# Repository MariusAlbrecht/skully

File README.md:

# skully

A split, wireless, ergo keybaord inspired by weteor's [3w6](https://github.com/weteor/3W6) and built with MrZealot's [ergogen](https://github.com/ergogen/ergogen).

The overall shape of one side reminded me of a skull, thus the name and silkscreen

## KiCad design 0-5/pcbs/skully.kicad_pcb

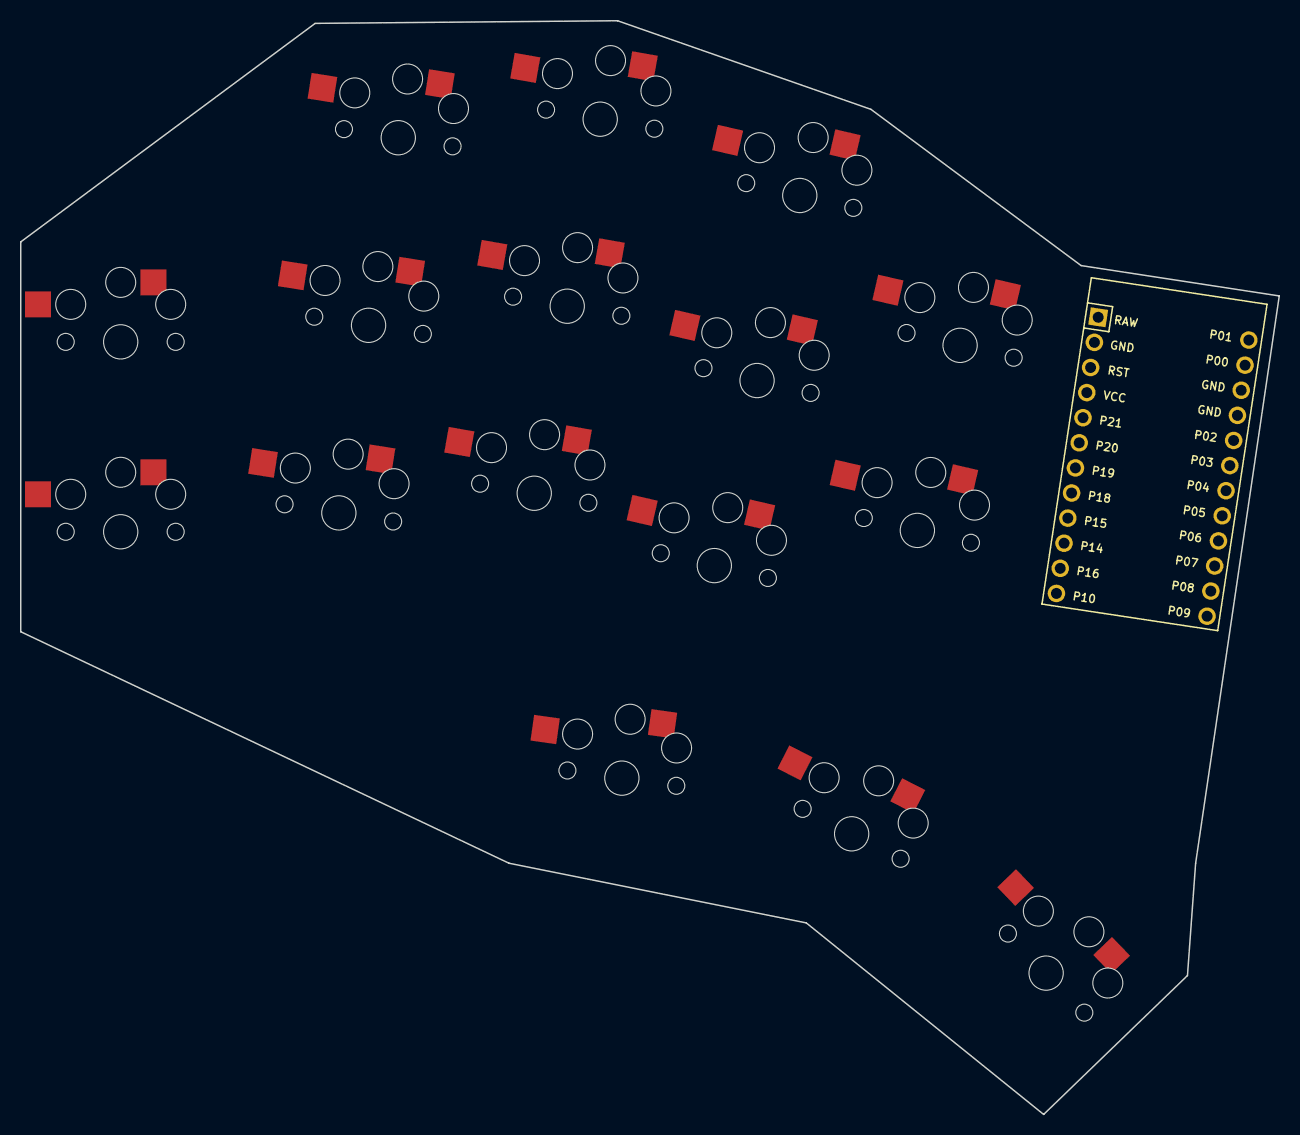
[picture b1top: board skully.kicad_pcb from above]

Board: 2 copper layers, 125.9 x 109.4 mm, 17 parts (0 on the bottom side), 14 nets, no tracks yet.

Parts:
MCU1: ProMicro
S1, S2, S3, S4, S5, S6, S7, S8, S9, S10, S11, S12, S13, S14, S15, S16: PG1350

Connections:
GND: MCU1.2, MCU1.15, MCU1.16, S1.2, S2.2, S3.2, S4.2, S5.2, S6.2, S7.2, S8.2, S9.2, S10.2, S11.2, S12.2, S13.2, S14.2, S15.2, S16.2
P0: MCU1.14, S3.1
P1: MCU1.13, S6.1
P2: MCU1.17, S9.1
P3: MCU1.18, S1.1
P4: MCU1.19, S4.1
P5: MCU1.20, S7.1
P6: MCU1.21, S10.1
P7: MCU1.22, S12.1
P8: MCU1.23, S2.1
P9: MCU1.24, S5.1
P10: MCU1.12, S8.1
P14: MCU1.10, S15.1
P15: MCU1.9, S16.1

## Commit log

2022-01-19 inti
2022-01-19 init
2022-01-31 outline
2022-02-04 "iterations" removed
2022-02-07 output
2022-02-07 yaml updates (pcb)
2022-02-07 readme
2022-02-07 ingnore
2022-02-07 ingores
2022-02-07 pics
2022-02-07 ignore
2022-02-07 fuck
2022-02-07 higher res
2022-02-07 fix syntax & row references
2022-02-07 test
2022-02-07 nothing
2022-02-08 little changes and new outputs
2022-02-08 keys footprint working somehow
2022-02-08 working config i think?
